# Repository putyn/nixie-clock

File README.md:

naked nixie
=========

IN4 nixie tube + ESP8266

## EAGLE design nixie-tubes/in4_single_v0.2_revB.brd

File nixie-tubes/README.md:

IN4 nixie tube PCB
------

1. in4_single_v0.1
	first version wth single nixie and power supply on the same board, idea was to test the power supplay and the driving circuit for nixies. Never made
2. in4_single_v0.2_revA
	second version which was manufactured at OSHPark, single nixie design made to be daisy chained
3. in4_single_v0.2_revB
	some improvements to version 0.2 (added another GND connection, some warning signs, change anode current limiting resistor to SMD, changed footprint for '595, reorderd schematic)

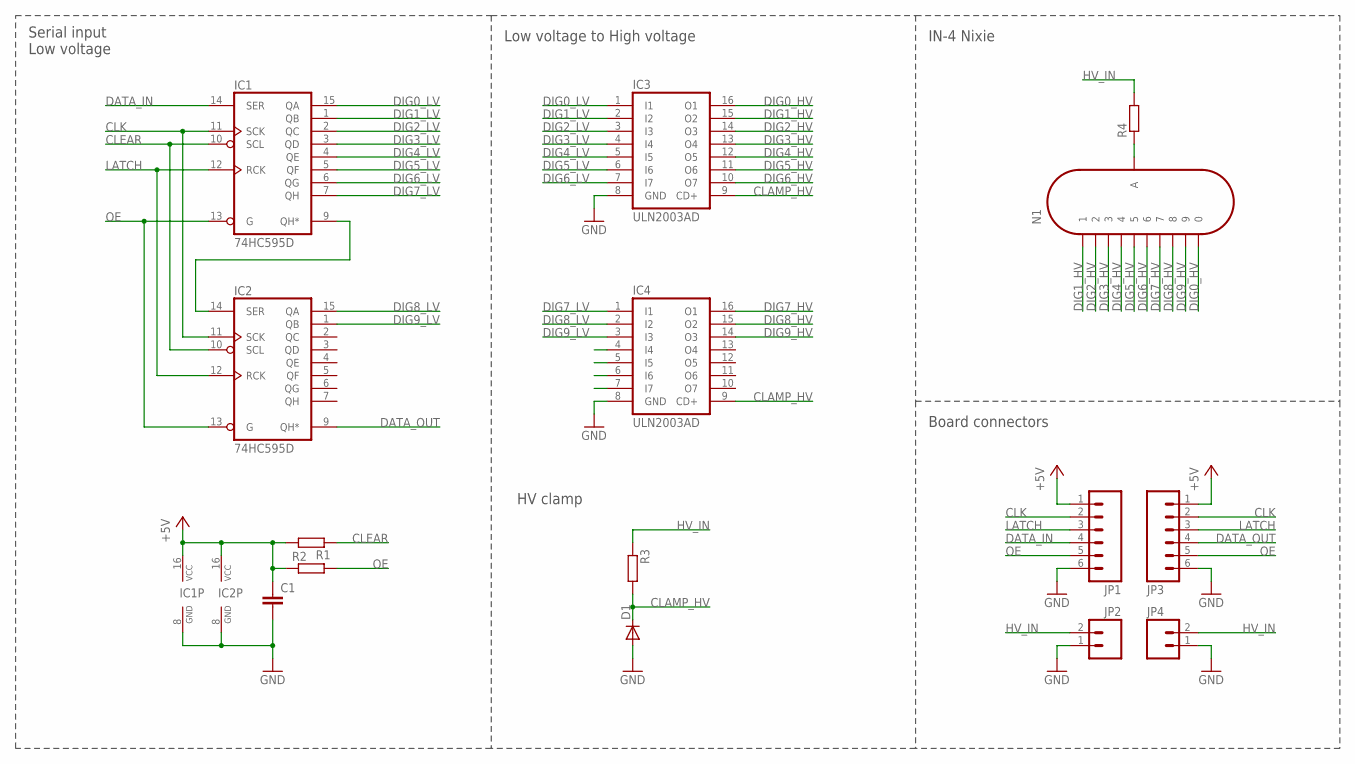
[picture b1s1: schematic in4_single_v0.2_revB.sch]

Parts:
C1: C-EUC0805; C0805
D1: DIODE-SOD-123; SOD-123
IC1, IC2: 74HC595D; SO16
IC3, IC4: ULN2003AD; SO16
JP1, JP3: M06NO_SILK_FEMALE_PTH; 1X06_NO_SILK
JP2, JP4: M021X02_NO_SILK; 1X02_NO_SILK
N1: IN-4
R1, R2, R3: R-EU_R0805; R0805
R4: R-EU_R1210; R1210

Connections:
+5V: C1.1, IC1.16 (VCC), IC2.16 (VCC), JP1.1, JP3.1, R1.2, R2.1
CLAMP_HV: D1.C, IC3.9 (CD+), IC4.9 (CD+), R3.2
CLEAR: IC1.10 (SCL), IC2.10 (SCL), R1.1
CLK: IC1.11 (SCK), IC2.11 (SCK), JP1.2, JP3.2
DATA_IN: IC1.14 (SER), JP1.4
DATA_OUT: IC2.9 (QH*), JP3.4
DIG0_HV: IC3.16 (O1), N1.8 (0)
DIG0_LV: IC1.15 (QA), IC3.1 (I1)
DIG1_HV: IC3.15 (O2), N1.14 (1)
DIG1_LV: IC1.1 (QB), IC3.2 (I2)
DIG2_HV: IC3.14 (O3), N1.9 (2)
DIG2_LV: IC1.2 (QC), IC3.3 (I3)
DIG3_HV: IC3.13 (O4), N1.11 (3)
DIG3_LV: IC1.3 (QD), IC3.4 (I4)
DIG4_HV: IC3.12 (O5), N1.1 (4)
DIG4_LV: IC1.4 (QE), IC3.5 (I5)
DIG5_HV: IC3.11 (O6), N1.12 (5)
DIG5_LV: IC1.5 (QF), IC3.6 (I6)
DIG6_HV: IC3.10 (O7), N1.2 (6)
DIG6_LV: IC1.6 (QG), IC3.7 (I7)
DIG7_HV: IC4.16 (O1), N1.6 (7)
DIG7_LV: IC1.7 (QH), IC4.1 (I1)
DIG8_HV: IC4.15 (O2), N1.3 (8)
DIG8_LV: IC2.15 (QA), IC4.2 (I2)
DIG9_HV: IC4.14 (O3), N1.5 (9)
DIG9_LV: IC2.1 (QB), IC4.3 (I3)
GND: C1.2, D1.A, IC1.8 (GND), IC2.8 (GND), IC3.8 (GND), IC4.8 (GND), JP1.6, JP2.1, JP3.6, JP4.1
HV_IN: JP2.2, JP4.2, R3.1, R4.2
LATCH: IC1.12 (RCK), IC2.12 (RCK), JP1.3, JP3.3
unnamed: IC1.9 (QH*), IC2.14 (SER)
unnamed: N1.4 (A), R4.1
OE: IC1.13 (G), IC2.13 (G), JP1.5, JP3.5, R2.2

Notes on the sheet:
Serial input Low voltage
Low voltage to High voltage
HV clamp
IN-4 Nixie
Board connectors

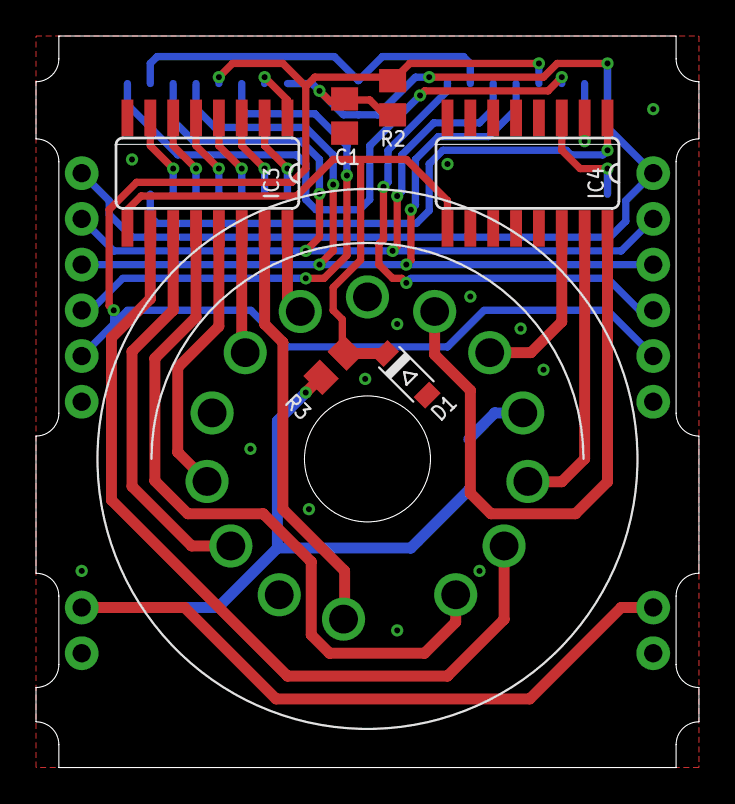
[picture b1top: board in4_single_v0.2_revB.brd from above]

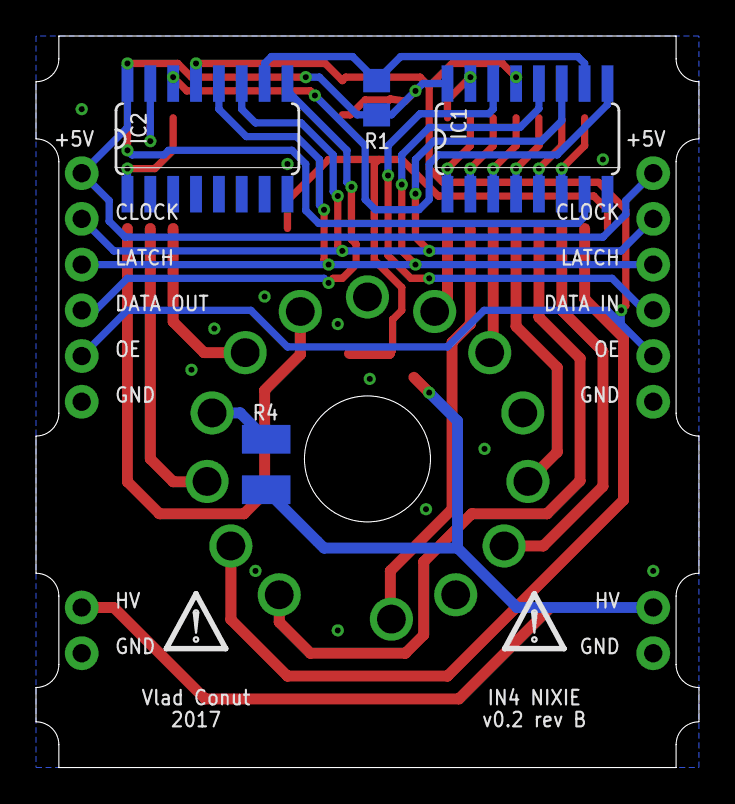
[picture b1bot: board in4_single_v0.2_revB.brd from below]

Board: 2 copper layers, 36.8 x 40.6 mm, 17 parts (6 on the bottom side), 32 nets.

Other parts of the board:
U$1, U$2: DANGER_LOGO

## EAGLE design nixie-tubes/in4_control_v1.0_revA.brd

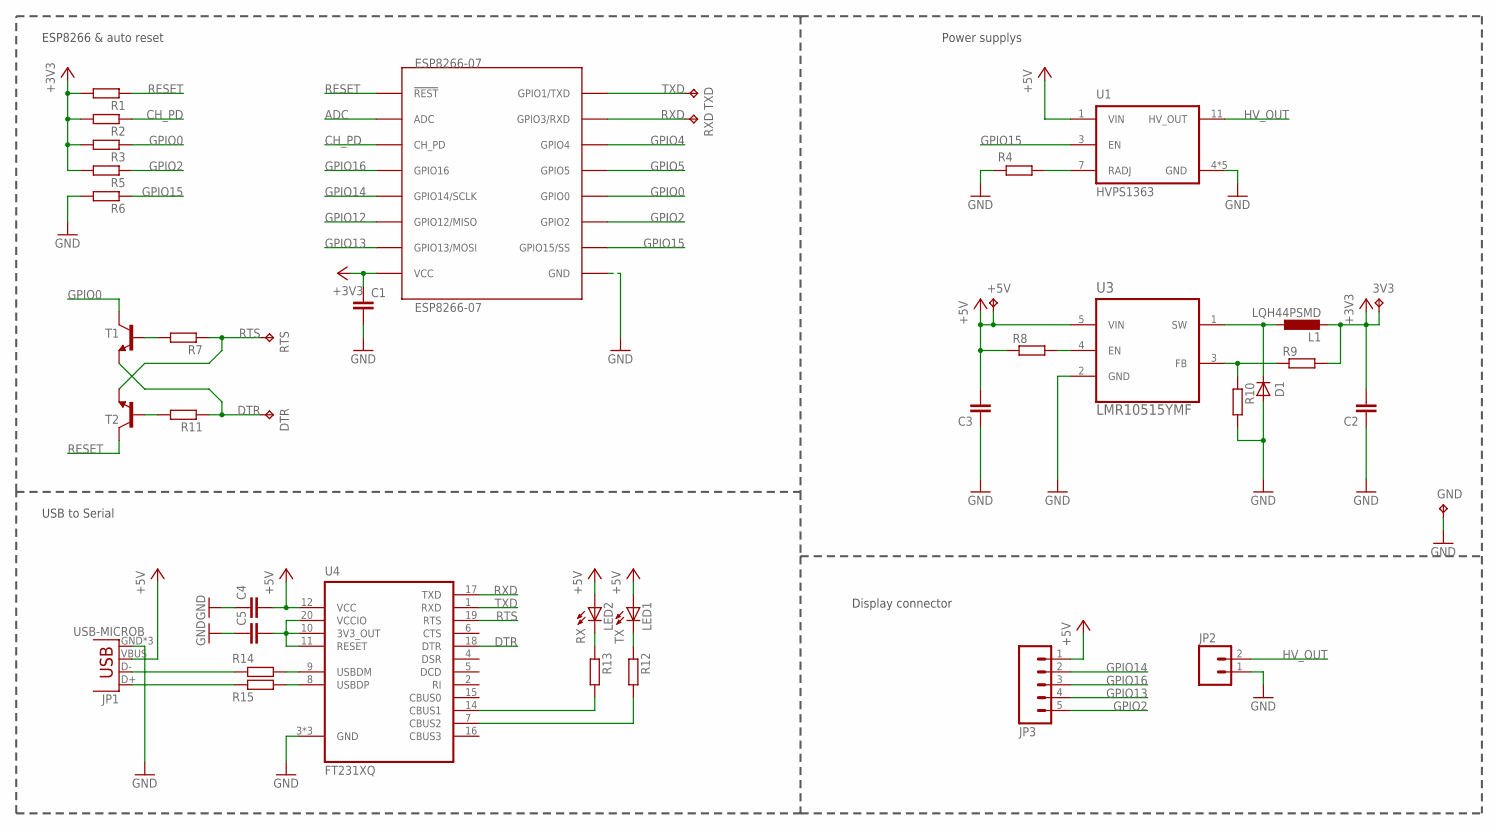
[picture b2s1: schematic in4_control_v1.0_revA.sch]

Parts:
3V3: TPTP15R; TP15R
+5V: TPTP17R; TP17R
C1, C2, C3: C-EUC0805; C0805
C4, C5: C-EUC0603; C0603
D1: DIODE-SOD-123; SOD-123
DTR: TPTP17R; TP17R
ESP8266-07: ESP8266-07; ESP07
GND: TPTP17R; TP17R
JP1: USB-MICROB
JP2: M021X02_NO_SILK; 1X02_NO_SILK
JP3: M05PTH; 1X05
L1: LQH44PSMD; 1515
LED1: TX; CHIP-LED0603
LED2: RX; CHIP-LED0603
R1, R2, R3, R4, R5, R6, R7, R8, R9, R10, R11, R12, R13, R14, R15: R-EU_R0603; R0603
RTS: TPTP17R; TP17R
RXD: TPTP17R; TP17R
T1, T2: MMBT3904LT1-NPN-SOT23-BEC; SOT23-BEC
TXD: TPTP17R; TP17R
U1: HVPS1363; HVPS-1363
U3: LMR10515YMF; SOT95P290X145-5N
U4: FT231XQ; QFN-20

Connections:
+3V3: 3V3.TP, C1.1, C2.2, ESP8266-07.VCC, L1.2, R1.2, R2.2, R3.2, R5.2, R9.2
+5V: +5V.TP, C3.2, C4.2, JP1.VBUS, JP3.1, LED1.A, LED2.A, R8.1, U1.1 (VIN), U3.5 (VIN), U4.12 (VCC)
ADC: ESP8266-07.ADC
CH_PD: ESP8266-07.CH_PD, R2.1
DTR: DTR.TP, R11.1, T1.E, U4.18 (DTR)
GND: C1.2, C2.1, C3.1, C4.1, C5.1, D1.A, ESP8266-07.GND, GND.TP, JP1.GND, JP1.MT1 (GND), JP1.MT2 (GND), JP2.1, R4.2, R6.2, R10.2, U1.4 (GND), U1.6 (GND), U1.8 (GND), U1.9 (GND), U1.10 (GND), U3.2 (GND), U4.3 (GND), U4.13 (GND), U4.21 (GND)
GPIO0: ESP8266-07.GPIO0, R3.1, T1.C
GPIO2: ESP8266-07.GPIO2, JP3.5, R5.1
GPIO4: ESP8266-07.GPIO4
GPIO5: ESP8266-07.GPIO5
GPIO12: ESP8266-07.GPIO12 (GPIO12/MISO)
GPIO13: ESP8266-07.GPIO13 (GPIO13/MOSI), JP3.4
GPIO14: ESP8266-07.GPIO14 (GPIO14/SCLK), JP3.2
GPIO15: ESP8266-07.GPIO15 (GPIO15/SS), R6.1, U1.3 (EN)
GPIO16: ESP8266-07.GPIO16, JP3.3
HV_OUT: JP2.2, U1.11 (HV_OUT)
unnamed: C5.2, U4.10 (3V3_OUT), U4.11 (RESET), U4.20 (VCCIO)
unnamed: R8.2, U3.4 (EN)
unnamed: R9.1, R10.1, U3.3 (FB)
unnamed: R14.1, U4.9 (USBDM)
unnamed: R15.1, U4.8 (USBDP)
unnamed: JP1.D+, R15.2
unnamed: JP1.D-, R14.2
unnamed: LED2.C, R13.1
unnamed: LED1.C, R12.1
unnamed: R13.2, U4.14 (CBUS1)
unnamed: R12.2, U4.7 (CBUS2)
unnamed: R4.1, U1.7 (RADJ)
unnamed: R11.2, T2.B
unnamed: R7.2, T1.B
RESET: ESP8266-07.REST (!REST!), R1.1, T2.C
RTS: R7.1, RTS.TP, T2.E, U4.19 (RTS)
RXD: ESP8266-07.RXD (GPIO3/RXD), RXD.TP, U4.17 (TXD)
SW: D1.C, L1.1, U3.1 (SW)
TXD: ESP8266-07.TXD (GPIO1/TXD), TXD.TP, U4.1 (RXD)

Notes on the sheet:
ESP8266 & auto reset
Display connector
USB to Serial
Power supplys

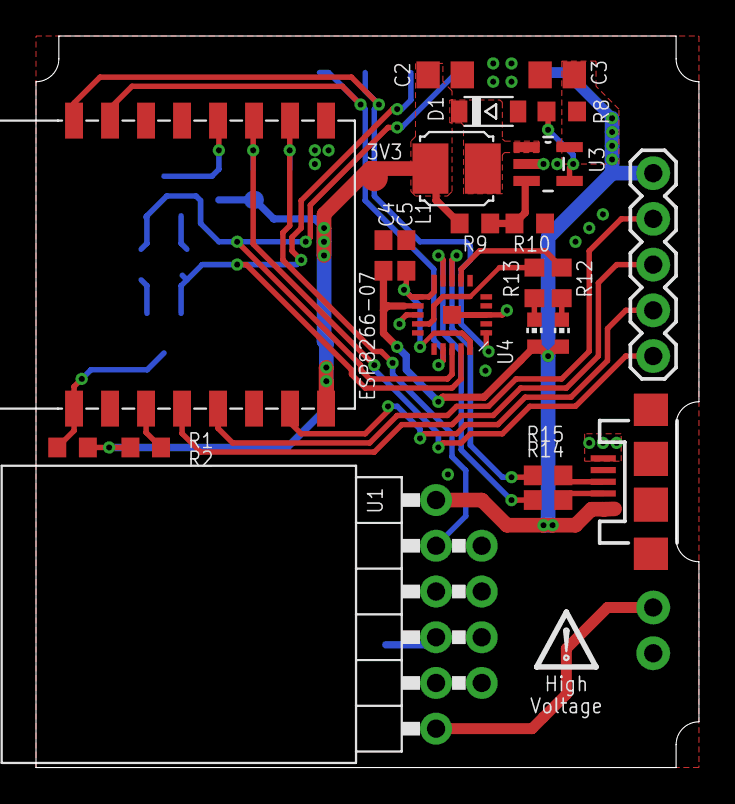
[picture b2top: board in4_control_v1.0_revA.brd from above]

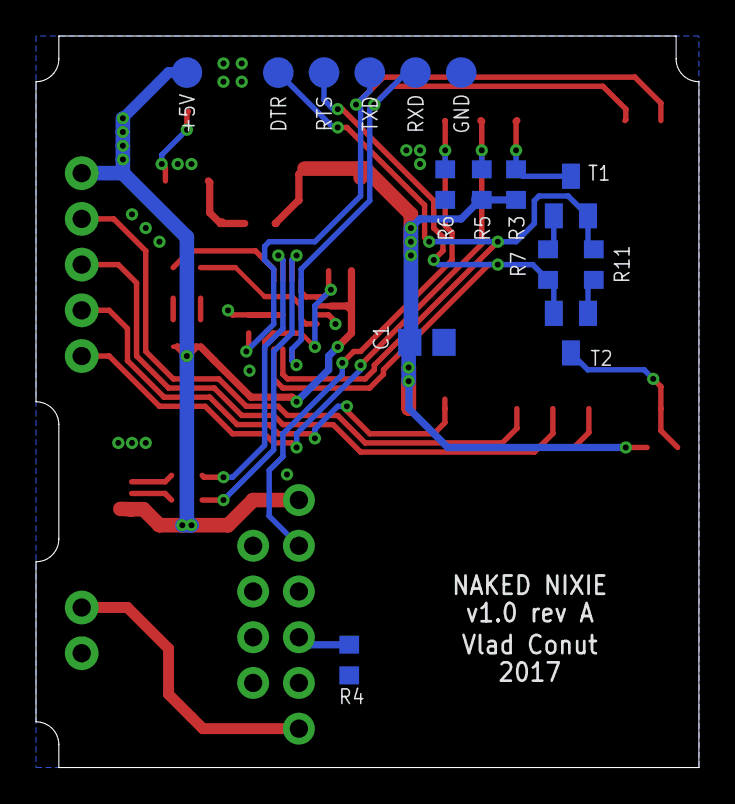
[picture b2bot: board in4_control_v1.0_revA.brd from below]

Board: 2 copper layers, 36.8 x 40.6 mm, 41 parts (15 on the bottom side), 31 nets.

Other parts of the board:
U$1: DANGER_LOGO

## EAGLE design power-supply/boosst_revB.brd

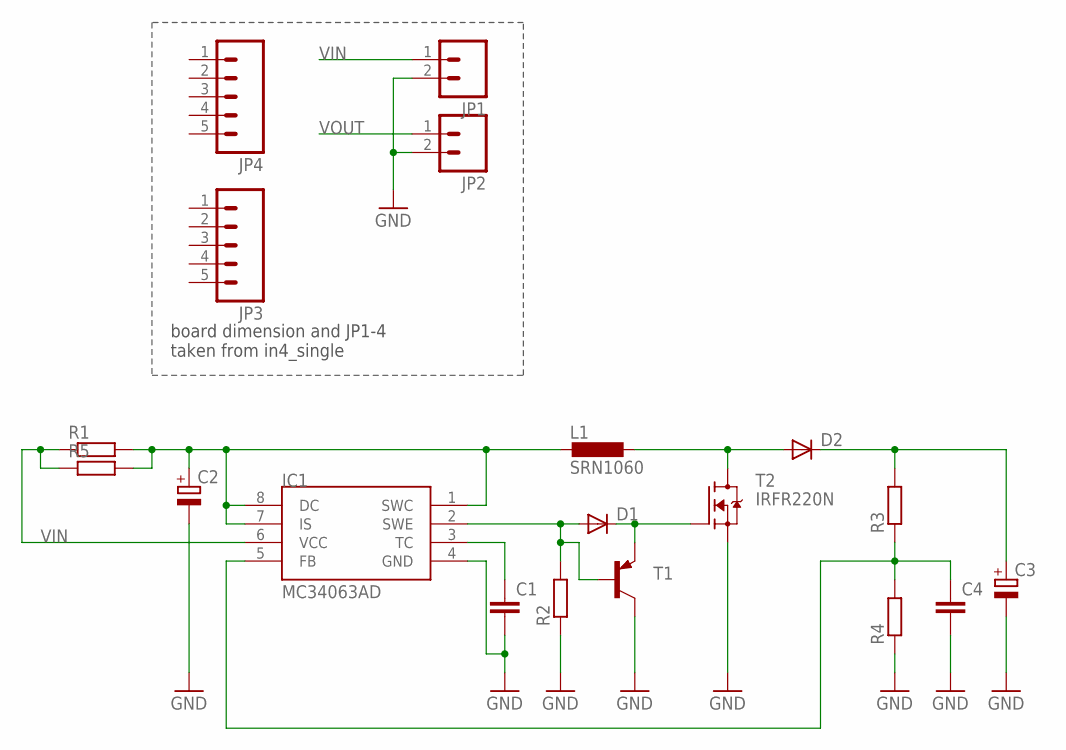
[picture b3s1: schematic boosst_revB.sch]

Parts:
C1, C4: C-EUC1206; C1206
C2: CPOL-EUE2.5-6; E2,5-6
C3: CPOL-EUE2,5-6E; E2,5-6E
D1: DIODE-SOD123; SOD123
D2: DIODE-SMB; SMB
IC1: MC34063AD; SOIC8
JP1, JP2: M02PTH; 1X02
JP3, JP4: M05PTH; 1X05
L1: SRN1060
R1, R5: R-EU_M1206; M1206
R2, R3, R4: R-EU_R1206; R1206
T1: MMBT3906LT1-PNP-SOT23-BEC; SOT23-BEC
T2: IRFR220N; DPACK

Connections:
GND: C1.2, C2.-, C3.-, C4.2, IC1.4 (GND), JP1.2, JP2.2, R2.1, R4.1, T1.C, T2.3 (S)
unnamed: D1.C, T1.E, T2.1 (G)
unnamed: D1.A, IC1.2 (SWE), R2.2, T1.B
unnamed: C1.1, IC1.3 (TC)
unnamed: C4.1, IC1.5 (FB), R3.1, R4.2
unnamed: C2.+, IC1.1 (SWC), IC1.7 (IS), IC1.8 (DC), L1.P$2 (2), R1.2, R5.2
SW: D2.A, L1.P$1 (1), T2.4 (D)
VIN: IC1.6 (VCC), JP1.1, R1.1, R5.1
VOUT: C3.+, D2.C, JP2.1, R3.2

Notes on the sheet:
board dimension and JP1-4 taken from in4_single

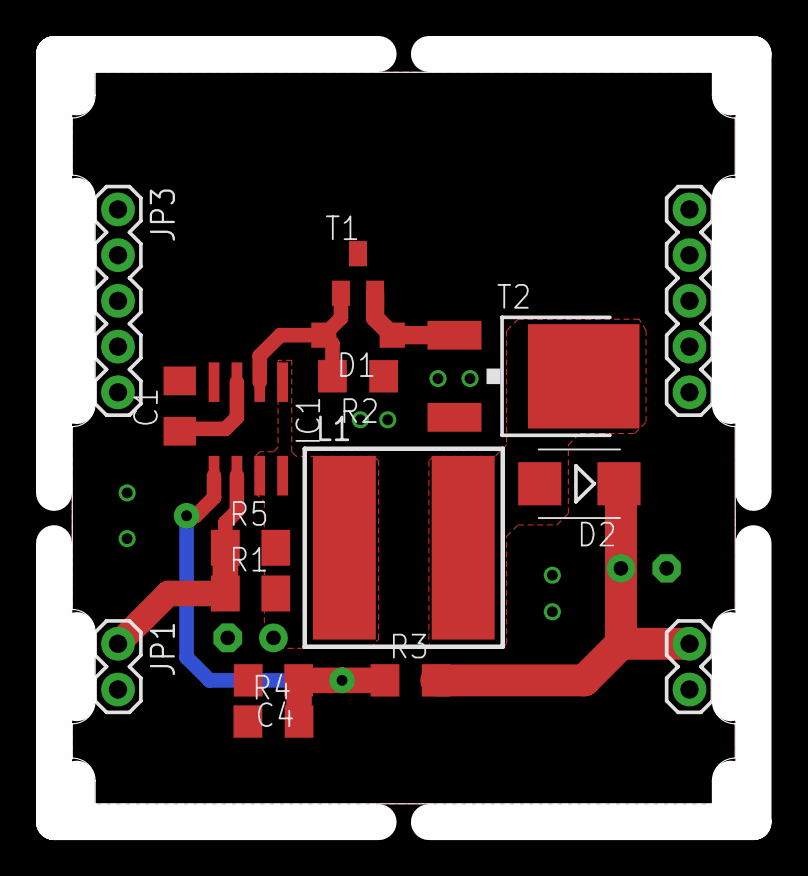
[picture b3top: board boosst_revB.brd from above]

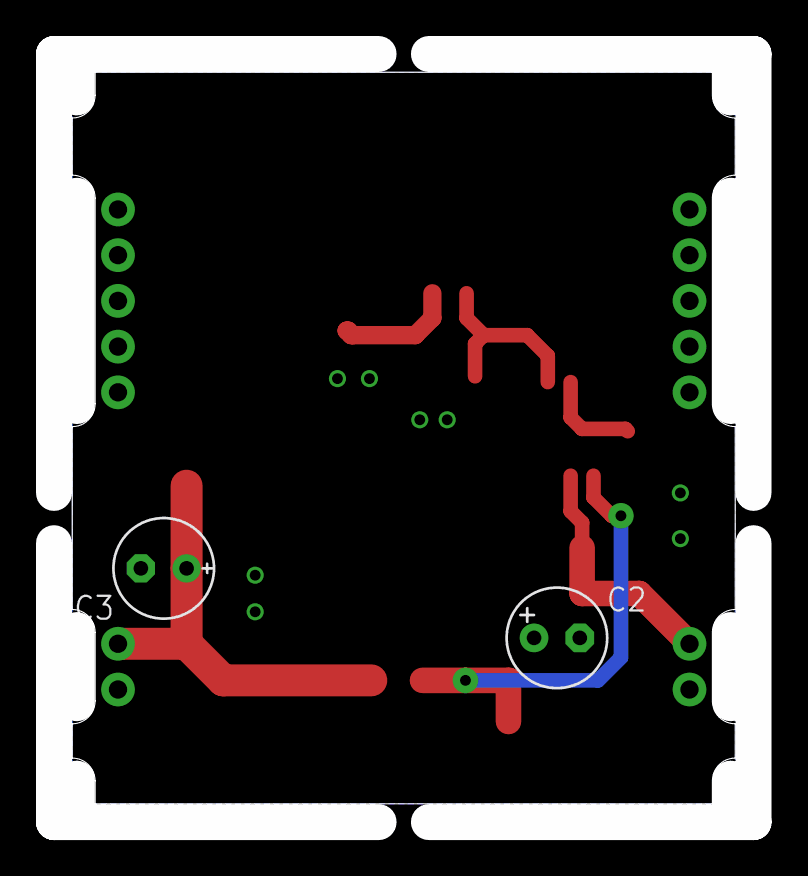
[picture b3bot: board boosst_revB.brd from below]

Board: 2 copper layers, 38.9 x 42.7 mm, 19 parts (2 on the bottom side), 9 nets.

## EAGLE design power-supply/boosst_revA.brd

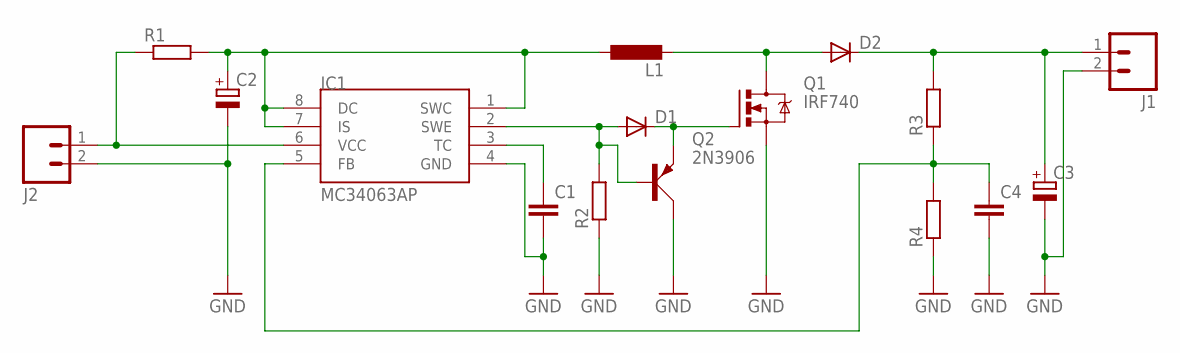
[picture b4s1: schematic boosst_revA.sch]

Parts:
C1, C4: C-EU025-025X050; C025-025X050
C2, C3: CPOL-EUE5-8.5; E5-8,5
D1: DIODE-D-5; D-5
D2: DIODE-DO41-7.6; DO41-7.6
IC1: MC34063AP; DIL08
J1, J2: M023.5MM; SCREWTERMINAL-3.5MM-2
L1: L-EU6000-XXX-RC; 6000-XXXX-RC
Q1: IRF740; TO220BV
Q2: 2N3906; TO92D
R1: R-EU_0309/10; 0309/10
R2: R-EU_0204/5; 0204/5
R3, R4: R-EU_0204/7; 0204/7

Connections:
GND: C1.2, C2.-, C3.-, C4.2, IC1.4 (GND), J1.2, J2.2, Q1.S, Q2.C, R2.1, R4.1
unnamed: C3.+, D2.C, J1.1, R3.2
unnamed: D1.C, Q1.G, Q2.E
unnamed: D1.A, IC1.2 (SWE), Q2.B, R2.2
unnamed: C1.1, IC1.3 (TC)
unnamed: C4.1, IC1.5 (FB), R3.1, R4.2
unnamed: C2.+, IC1.1 (SWC), IC1.7 (IS), IC1.8 (DC), L1.1, R1.2
unnamed: D2.A, L1.2, Q1.D
VIN: IC1.6 (VCC), J2.1, R1.1

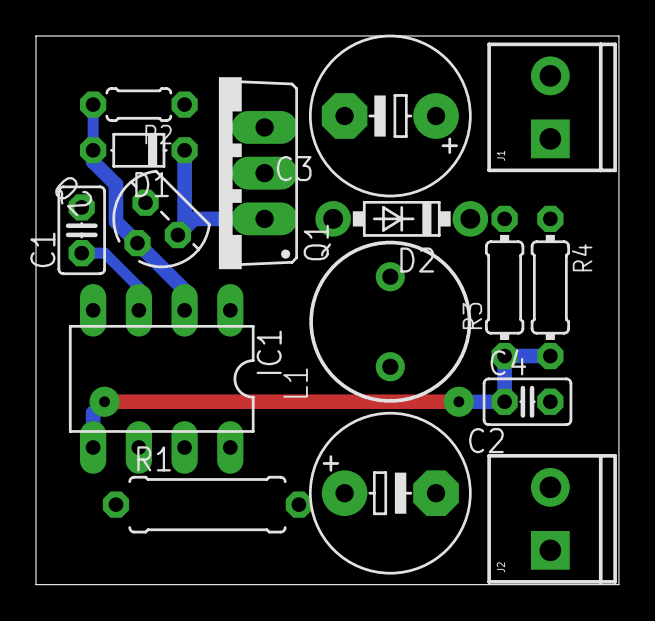
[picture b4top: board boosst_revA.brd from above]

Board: 2 copper layers, 32.4 x 30.5 mm, 16 parts (0 on the bottom side), 9 nets.

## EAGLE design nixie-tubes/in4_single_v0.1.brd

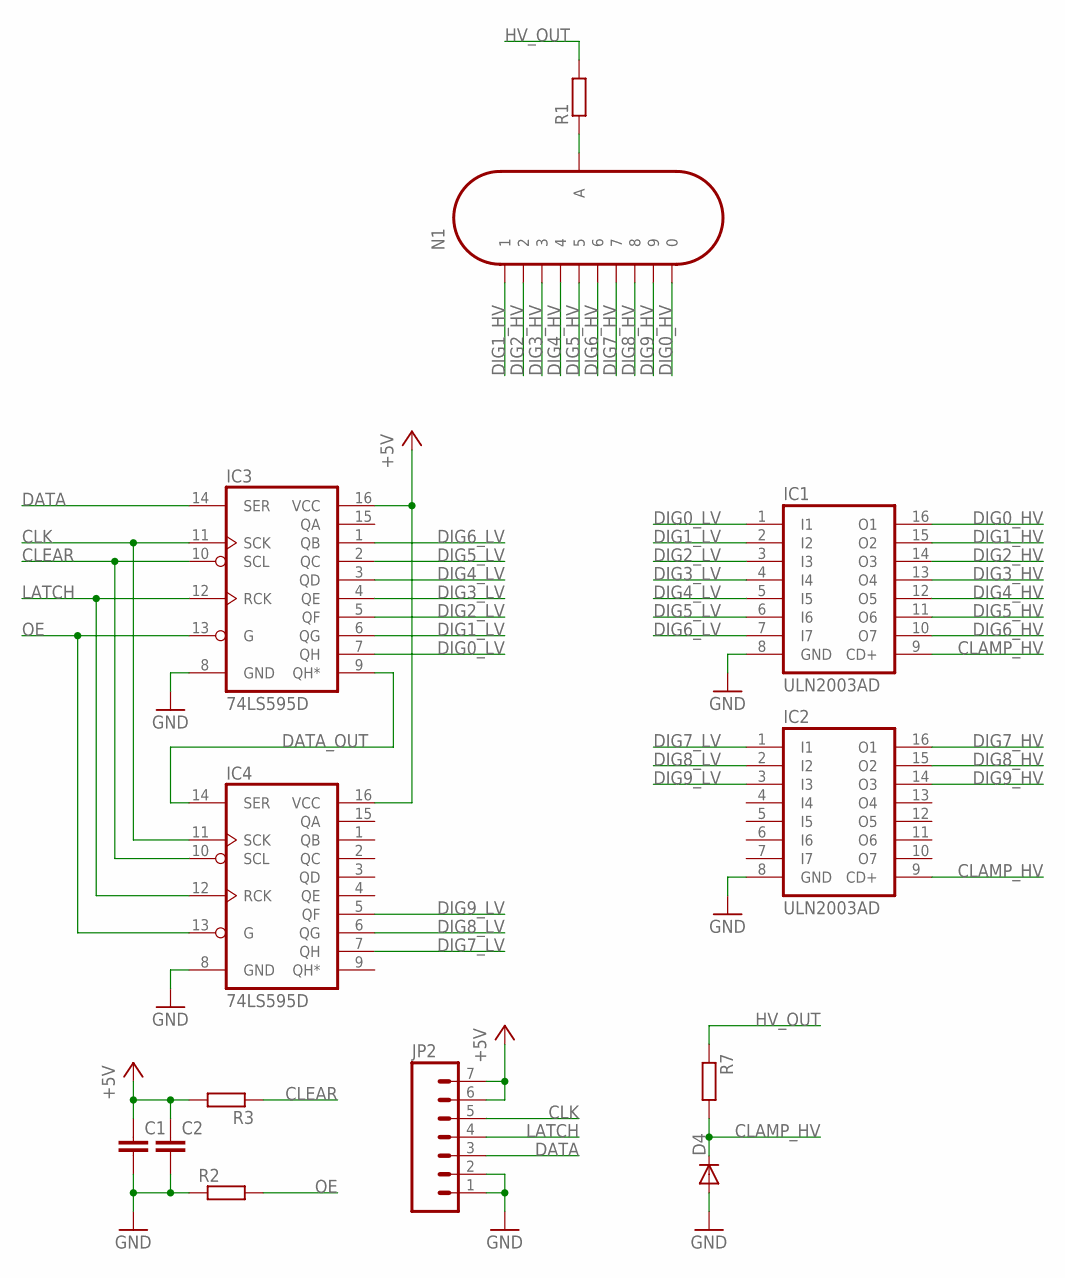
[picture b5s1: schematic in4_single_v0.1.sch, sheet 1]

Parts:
C1, C2: C-EUC0805; C0805
D4: DIODE-SOD-123; SOD-123
IC1, IC2: ULN2003AD; SO16
IC3, IC4: 74LS595D; SO16
JP2: M07LOCK; 1X07_LOCK
N1: IN-4
R1: R-EU_0204/7; 0204/7
R2, R3, R7: R-EU_R0805; R0805

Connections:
+5V: C1.1, C2.1, IC3.16 (VCC), IC4.16 (VCC), JP2.6, JP2.7, R3.2; also elsewhere on the board
CLAMP_HV: D4.C, IC1.9 (CD+), IC2.9 (CD+), R7.2
CLEAR: IC3.10 (SCL), IC4.10 (SCL), R3.1
CLK: IC3.11 (SCK), IC4.11 (SCK), JP2.5
DATA: IC3.14 (SER), JP2.3
DATA_OUT: IC3.9 (QH*), IC4.14 (SER)
DIG0_HV: IC1.16 (O1), N1.8 (0)
DIG0_LV: IC1.1 (I1), IC3.7 (QH)
DIG1_HV: IC1.15 (O2), N1.14 (1)
DIG1_LV: IC1.2 (I2), IC3.6 (QG)
DIG2_HV: IC1.14 (O3), N1.9 (2)
DIG2_LV: IC1.3 (I3), IC3.5 (QF)
DIG3_HV: IC1.13 (O4), N1.11 (3)
DIG3_LV: IC1.4 (I4), IC3.4 (QE)
DIG4_HV: IC1.12 (O5), N1.1 (4)
DIG4_LV: IC1.5 (I5), IC3.3 (QD)
DIG5_HV: IC1.11 (O6), N1.12 (5)
DIG5_LV: IC1.6 (I6), IC3.2 (QC)
DIG6_HV: IC1.10 (O7), N1.2 (6)
DIG6_LV: IC1.7 (I7), IC3.1 (QB)
DIG7_HV: IC2.16 (O1), N1.6 (7)
DIG7_LV: IC2.1 (I1), IC4.7 (QH)
DIG8_HV: IC2.15 (O2), N1.3 (8)
DIG8_LV: IC2.2 (I2), IC4.6 (QG)
DIG9_HV: IC2.14 (O3), N1.5 (9)
DIG9_LV: IC2.3 (I3), IC4.5 (QF)
GND: C1.2, C2.2, D4.A, IC1.8 (GND), IC2.8 (GND), IC3.8 (GND), IC4.8 (GND), JP2.1, JP2.2, R2.1; also elsewhere on the board
HV_OUT: R1.2, R7.1; also elsewhere on the board
LATCH: IC3.12 (RCK), IC4.12 (RCK), JP2.4
unnamed: N1.4 (A), R1.1
OE: IC3.13 (G), IC4.13 (G), R2.2

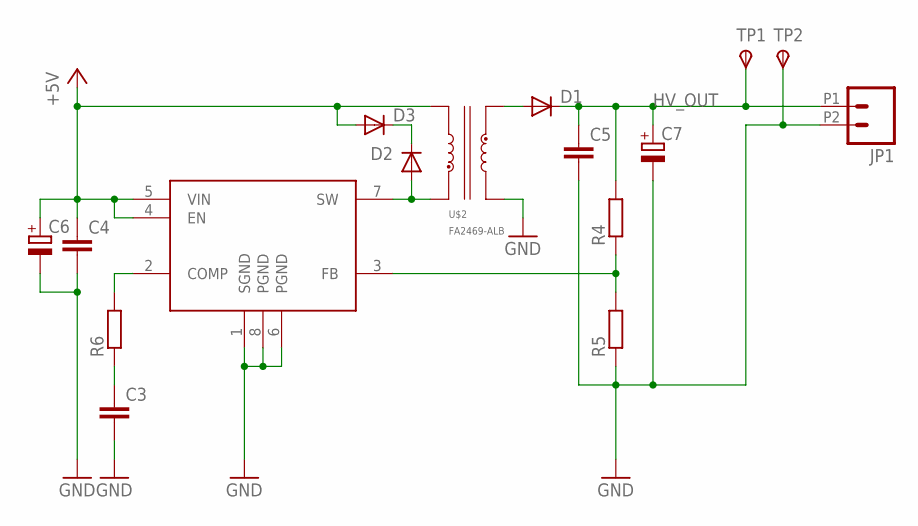
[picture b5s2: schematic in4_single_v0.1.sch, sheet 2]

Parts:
C3: C-EUC0805; C0805
C4, C5: C-EUC1210; C1210
C6, C7: CPOL-EUE2.5-5; E2,5-5
D1: DIODE-DO-214AC; DO-214AC
D2, D3: DIODE-SOD-123; SOD-123
IC5: MC3172YM; SOIC8
JP1: M022.54MM_SCREWTERM; 1X02_2.54_SCREWTERM
R4, R5, R6: R-EU_R0805; R0805
TP1, TP2: TPSPAD1-13; P1-13
U$2: FA2469-ALB; FA2469

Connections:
+5V: C4.1, C6.+, D3.A, IC5.4 (EN), IC5.5 (VIN), U$2.3; also elsewhere on the board
GND: C3.2, C4.2, C5.2, C6.-, C7.-, IC5.1 (SGND), IC5.6 (PGND), IC5.8 (PGND), JP1.P2 (2), R5.1, TP2.TP, U$2.6; also elsewhere on the board
HV_OUT: C5.1, C7.+, D1.1 (C), JP1.P1 (1), R4.2, TP1.TP; also elsewhere on the board
unnamed: D2.C, D3.C
unnamed: D1.2 (A), U$2.4
unnamed: IC5.2 (COMP), R6.2
unnamed: IC5.3 (FB), R4.1, R5.2
unnamed: C3.1, R6.1
SW: D2.A, IC5.7 (SW), U$2.1

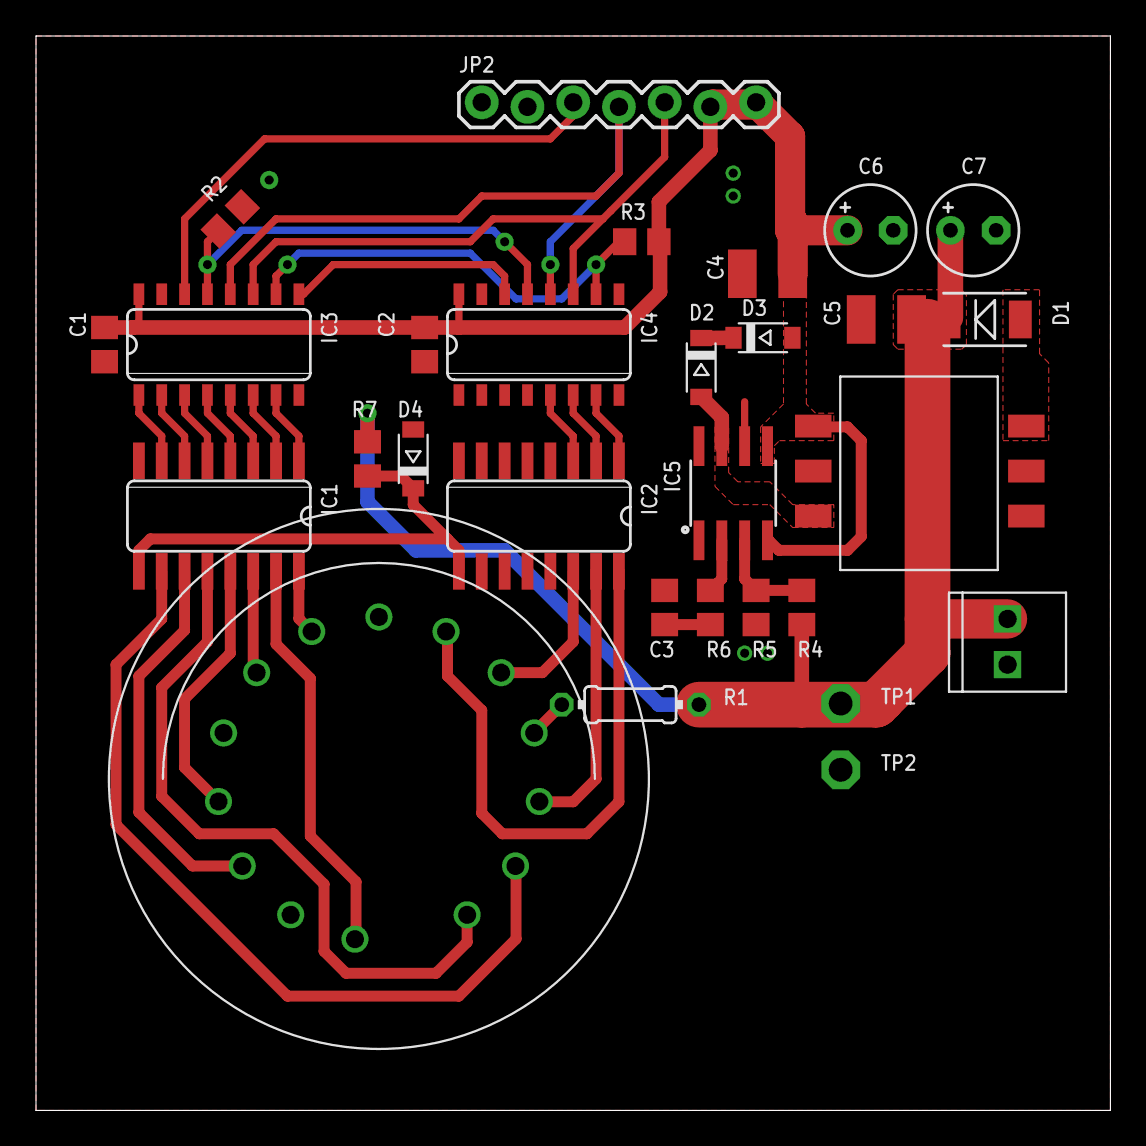
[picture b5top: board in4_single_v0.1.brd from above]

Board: 2 copper layers, 59.7 x 59.7 mm, 29 parts (0 on the bottom side), 37 nets.

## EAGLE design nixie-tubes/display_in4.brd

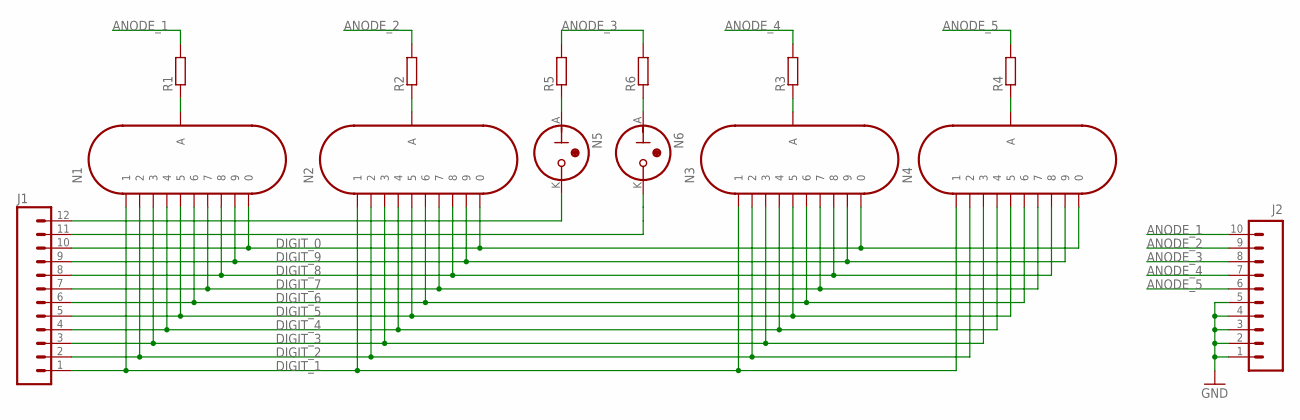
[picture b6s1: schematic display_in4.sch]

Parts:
J1: M12LOCK; 1X12_LOCK
J2: M10LOCK; 1X10_LOCK
N1, N2, N3, N4: IN-4
N5, N6: IN-6
R1, R2, R3, R4, R5, R6: R-EU_0204/7; 0204/7

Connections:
ANODE_1: J2.10, R1.2
ANODE_2: J2.9, R2.2
ANODE_3: J2.8, R5.2, R6.2
ANODE_4: J2.7, R3.2
ANODE_5: J2.6, R4.2
DIGIT_0: J1.10, N1.8 (0), N2.8 (0), N3.8 (0), N4.8 (0)
DIGIT_1: J1.1, N1.14 (1), N2.14 (1), N3.14 (1), N4.14 (1)
DIGIT_2: J1.2, N1.9 (2), N2.9 (2), N3.9 (2), N4.9 (2)
DIGIT_3: J1.3, N1.11 (3), N2.11 (3), N3.11 (3), N4.11 (3)
DIGIT_4: J1.4, N1.1 (4), N2.1 (4), N3.1 (4), N4.1 (4)
DIGIT_5: J1.5, N1.12 (5), N2.12 (5), N3.12 (5), N4.12 (5)
DIGIT_6: J1.6, N1.2 (6), N2.2 (6), N3.2 (6), N4.2 (6)
DIGIT_7: J1.7, N1.6 (7), N2.6 (7), N3.6 (7), N4.6 (7)
DIGIT_8: J1.8, N1.3 (8), N2.3 (8), N3.3 (8), N4.3 (8)
DIGIT_9: J1.9, N1.5 (9), N2.5 (9), N3.5 (9), N4.5 (9)
GND: J2.1, J2.2, J2.3, J2.4, J2.5
unnamed: J1.12, N5.K
unnamed: J1.11, N6.K
unnamed: N6.A, R6.1
unnamed: N5.A, R5.1
unnamed: N1.4 (A), R1.1
unnamed: N2.4 (A), R2.1
unnamed: N3.4 (A), R3.1
unnamed: N4.4 (A), R4.1

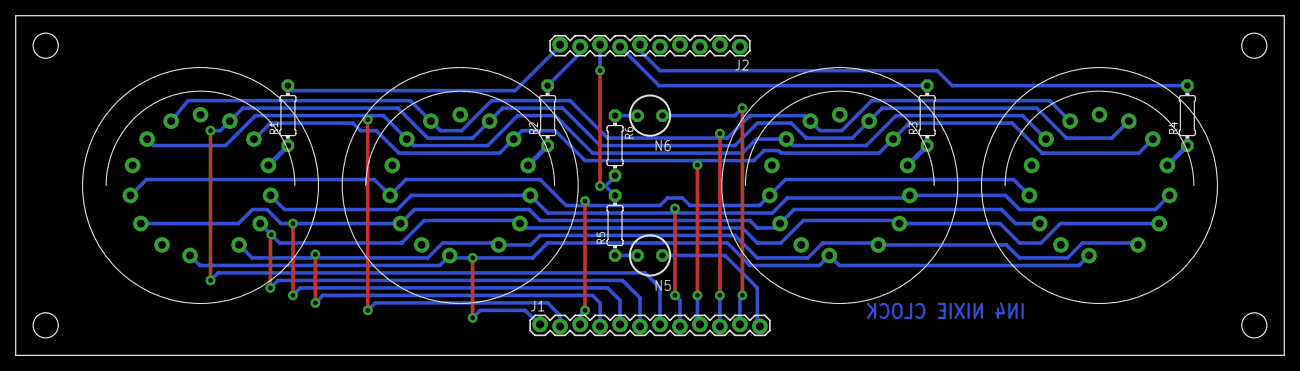
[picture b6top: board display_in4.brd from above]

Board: 2 copper layers, 161.3 x 43.2 mm, 14 parts (0 on the bottom side), 24 nets.

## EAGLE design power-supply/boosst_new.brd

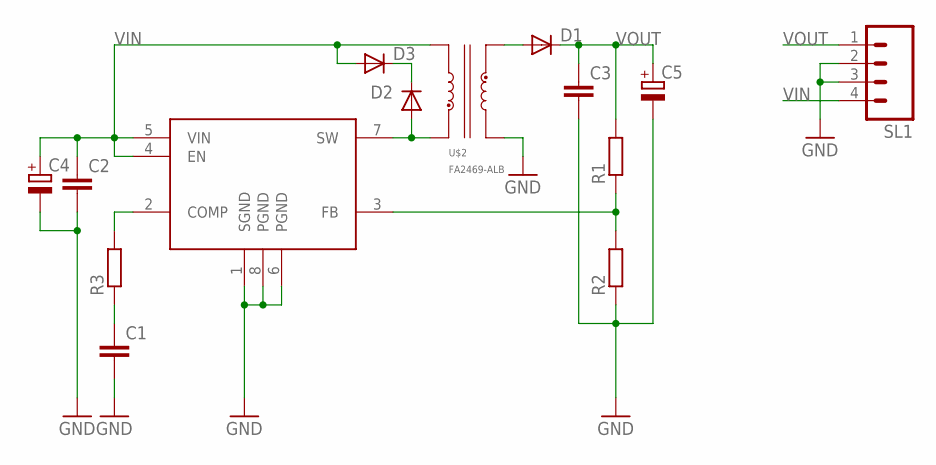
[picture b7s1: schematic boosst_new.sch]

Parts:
C1: C-EUC0805; C0805
C2, C3: C-EUC1210; C1210
C4, C5: CPOL-EUE2.5-5; E2,5-5
D1: DIODE-DO-214AC; DO-214AC
D2, D3: DIODE-SOD-123; SOD-123
R1, R2, R3: R-EU_R0805; R0805
SL1: M04; 04P
U$1: MC3172YM; SOIC8
U$2: FA2469-ALB; FA2469

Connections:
GND: C1.2, C2.2, C3.2, C4.-, C5.-, R2.1, SL1.2, SL1.3, U$1.1 (SGND), U$1.6 (PGND), U$1.8 (PGND), U$2.6
unnamed: D2.C, D3.C
unnamed: D1.2 (A), U$2.4
unnamed: R3.2, U$1.2 (COMP)
unnamed: R1.1, R2.2, U$1.3 (FB)
unnamed: C1.1, R3.1
SW: D2.A, U$1.7 (SW), U$2.1
VIN: C2.1, C4.+, D3.A, SL1.4, U$1.4 (EN), U$1.5 (VIN), U$2.3
VOUT: C3.1, C5.+, D1.1 (C), R1.2, SL1.1

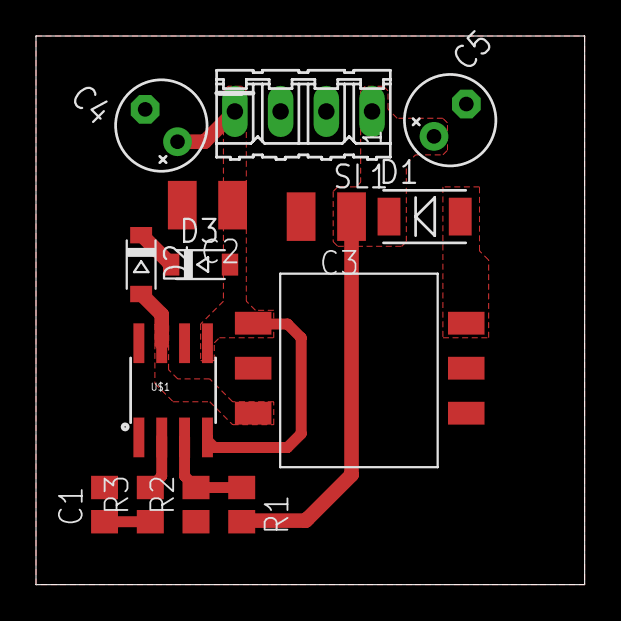
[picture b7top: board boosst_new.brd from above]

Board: 2 copper layers, 30.5 x 30.5 mm, 14 parts (0 on the bottom side), 9 nets.

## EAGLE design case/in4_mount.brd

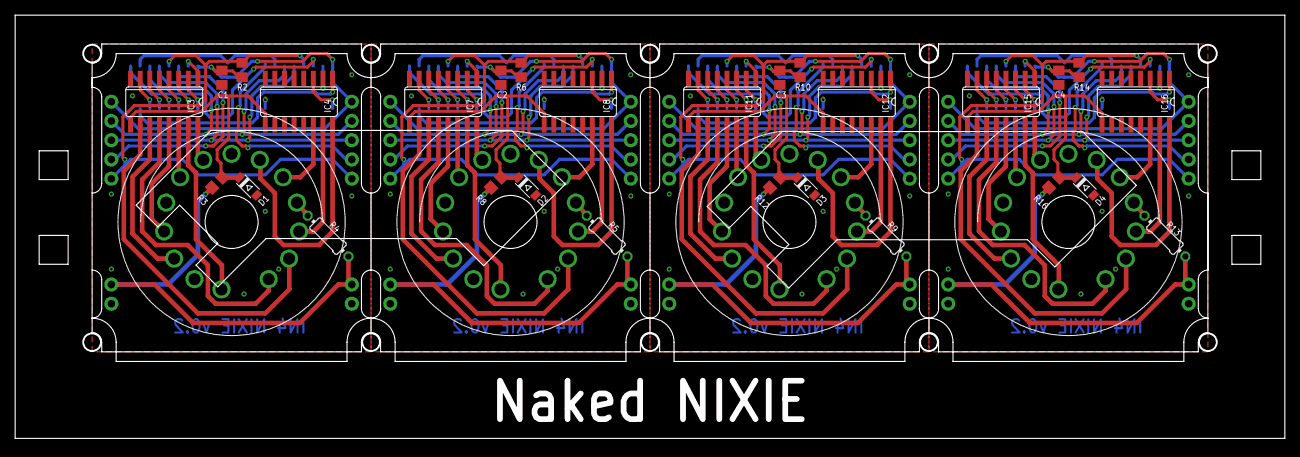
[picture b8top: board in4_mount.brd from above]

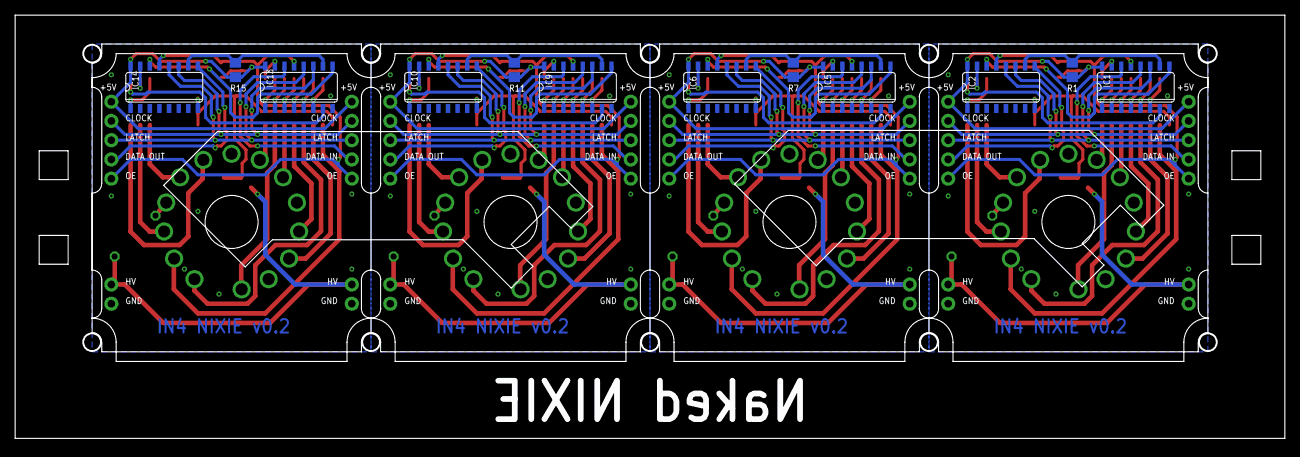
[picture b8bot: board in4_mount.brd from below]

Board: 2 copper layers, 167.4 x 56.1 mm, 60 parts (12 on the bottom side), 128 nets.

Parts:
C1, C2, C3, C4: C0805
D1, D2, D3, D4: SOD-123
IC1, IC2, IC5, IC6, IC9, IC10, IC13, IC14: 74HC595D; SO16
IC3, IC4, IC7, IC8, IC11, IC12, IC15, IC16: ULN2003AD; SO16
JP1, JP3, JP5, JP6, JP9, JP10, JP13, JP14: 1X05_NO_SILK
JP2, JP4, JP7, JP8, JP11, JP12, JP15, JP16: 1X02_NO_SILK
N1, N2, N3, N4: IN-4
R1, R2, R3, R6, R7, R8, R10, R11, R12, R14, R15, R16: R0805
R4, R5, R9, R13: 0204/7

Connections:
+5V: C1.1, IC1.16, IC2.16, JP1.1, JP3.1, R1.2, R2.1
+5V1: C2.1, IC5.16, IC6.16, JP5.1, JP6.1, R6.1, R7.2
+5V2: C3.1, IC9.16, IC10.16, JP9.1, JP10.1, R10.1, R11.2
+5V3: C4.1, IC13.16, IC14.16, JP13.1, JP14.1, R14.1, R15.2
CLAMP_HV: D1.C, IC3.9, IC4.9, R3.2
CLAMP_HV1: D2.C, IC7.9, IC8.9, R8.2
CLAMP_HV2: D3.C, IC11.9, IC12.9, R12.2
CLAMP_HV3: D4.C, IC15.9, IC16.9, R16.2
CLEAR: IC1.10, IC2.10, R1.1
CLEAR1: IC5.10, IC6.10, R7.1
CLEAR2: IC9.10, IC10.10, R11.1
CLEAR3: IC13.10, IC14.10, R15.1
CLK: IC1.11, IC2.11, JP1.2, JP3.2
CLK1: IC5.11, IC6.11, JP5.2, JP6.2
CLK2: IC9.11, IC10.11, JP9.2, JP10.2
CLK3: IC13.11, IC14.11, JP13.2, JP14.2
DATA_IN: IC1.14, JP1.4
DATA_IN1: IC5.14, JP5.4
DATA_IN2: IC9.14, JP9.4
DATA_IN3: IC13.14, JP13.4
DATA_OUT: IC2.9, JP3.4
DATA_OUT1: IC6.9, JP6.4
DATA_OUT2: IC10.9, JP10.4
DATA_OUT3: IC14.9, JP14.4
DIG0_HV: IC3.16, N1.8
DIG0_HV1: IC7.16, N2.8
DIG0_HV2: IC11.16, N3.8
DIG0_HV3: IC15.16, N4.8
DIG0_LV: IC1.15, IC3.1
DIG0_LV1: IC5.15, IC7.1
DIG0_LV2: IC9.15, IC11.1
DIG0_LV3: IC13.15, IC15.1
DIG1_HV: IC3.15, N1.14
DIG1_HV1: IC7.15, N2.14
DIG1_HV2: IC11.15, N3.14
DIG1_HV3: IC15.15, N4.14
DIG1_LV: IC1.1, IC3.2
DIG1_LV1: IC5.1, IC7.2
DIG1_LV2: IC9.1, IC11.2
DIG1_LV3: IC13.1, IC15.2
DIG2_HV: IC3.14, N1.9
DIG2_HV1: IC7.14, N2.9
DIG2_HV2: IC11.14, N3.9
DIG2_HV3: IC15.14, N4.9
DIG2_LV: IC1.2, IC3.3
DIG2_LV1: IC5.2, IC7.3
DIG2_LV2: IC9.2, IC11.3
DIG2_LV3: IC13.2, IC15.3
DIG3_HV: IC3.13, N1.11
DIG3_HV1: IC7.13, N2.11
DIG3_HV2: IC11.13, N3.11
DIG3_HV3: IC15.13, N4.11
DIG3_LV: IC1.3, IC3.4
DIG3_LV1: IC5.3, IC7.4
DIG3_LV2: IC9.3, IC11.4
DIG3_LV3: IC13.3, IC15.4
DIG4_HV: IC3.12, N1.1
DIG4_HV1: IC7.12, N2.1
DIG4_HV2: IC11.12, N3.1
DIG4_HV3: IC15.12, N4.1
DIG4_LV: IC1.4, IC3.5
DIG4_LV1: IC5.4, IC7.5
DIG4_LV2: IC9.4, IC11.5
DIG4_LV3: IC13.4, IC15.5
DIG5_HV: IC3.11, N1.12
DIG5_HV1: IC7.11, N2.12
DIG5_HV2: IC11.11, N3.12
DIG5_HV3: IC15.11, N4.12
DIG5_LV: IC1.5, IC3.6
DIG5_LV1: IC5.5, IC7.6
DIG5_LV2: IC9.5, IC11.6
DIG5_LV3: IC13.5, IC15.6
DIG6_HV: IC3.10, N1.2
DIG6_HV1: IC7.10, N2.2
DIG6_HV2: IC11.10, N3.2
DIG6_HV3: IC15.10, N4.2
DIG6_LV: IC1.6, IC3.7
DIG6_LV1: IC5.6, IC7.7
DIG6_LV2: IC9.6, IC11.7
DIG6_LV3: IC13.6, IC15.7
DIG7_HV: IC4.16, N1.6
DIG7_HV1: IC8.16, N2.6
DIG7_HV2: IC12.16, N3.6
DIG7_HV3: IC16.16, N4.6
DIG7_LV: IC1.7, IC4.1
DIG7_LV1: IC5.7, IC8.1
DIG7_LV2: IC9.7, IC12.1
DIG7_LV3: IC13.7, IC16.1
DIG8_HV: IC4.15, N1.3
DIG8_HV1: IC8.15, N2.3
DIG8_HV2: IC12.15, N3.3
DIG8_HV3: IC16.15, N4.3
DIG8_LV: IC2.15, IC4.2
DIG8_LV1: IC6.15, IC8.2
DIG8_LV2: IC10.15, IC12.2
DIG8_LV3: IC14.15, IC16.2
DIG9_HV: IC4.14, N1.5
DIG9_HV1: IC8.14, N2.5
DIG9_HV2: IC12.14, N3.5
DIG9_HV3: IC16.14, N4.5
DIG9_LV: IC2.1, IC4.3
DIG9_LV1: IC6.1, IC8.3
DIG9_LV2: IC10.1, IC12.3
DIG9_LV3: IC14.1, IC16.3
GND: C1.2, D1.A, IC1.8, IC2.8, IC3.8, IC4.8, JP2.1, JP4.1
GND1: C2.2, D2.A, IC5.8, IC6.8, IC7.8, IC8.8, JP7.1, JP8.1
GND2: C3.2, D3.A, IC9.8, IC10.8, IC11.8, IC12.8, JP11.1, JP12.1
GND3: C4.2, D4.A, IC13.8, IC14.8, IC15.8, IC16.8, JP15.1, JP16.1
HV_IN: JP2.2, JP4.2, R3.1, R4.2
HV_IN1: JP7.2, JP8.2, R5.2, R8.1
HV_IN2: JP11.2, JP12.2, R9.2, R12.1
HV_IN3: JP15.2, JP16.2, R13.2, R16.1
LATCH: IC1.12, IC2.12, JP1.3, JP3.3
LATCH1: IC5.12, IC6.12, JP5.3, JP6.3
LATCH2: IC9.12, IC10.12, JP9.3, JP10.3
LATCH3: IC13.12, IC14.12, JP13.3, JP14.3
unnamed: IC1.9, IC2.14
unnamed: N2.4, R5.1
unnamed: IC5.9, IC6.14
unnamed: N1.4, R4.1
unnamed: N3.4, R9.1
unnamed: IC9.9, IC10.14
unnamed: N4.4, R13.1
unnamed: IC13.9, IC14.14
OE: IC1.13, IC2.13, JP1.5, JP3.5, R2.2
OE1: IC5.13, IC6.13, JP5.5, JP6.5, R6.2
OE2: IC9.13, IC10.13, JP9.5, JP10.5, R10.2
OE3: IC13.13, IC14.13, JP13.5, JP14.5, R14.2

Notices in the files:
parts and their libraries:
SparkFun-DigitalIC: Licensing: Creative Commons ShareAlike 4.0 International - https://creativecommons.org/licenses/by-sa/4.0
